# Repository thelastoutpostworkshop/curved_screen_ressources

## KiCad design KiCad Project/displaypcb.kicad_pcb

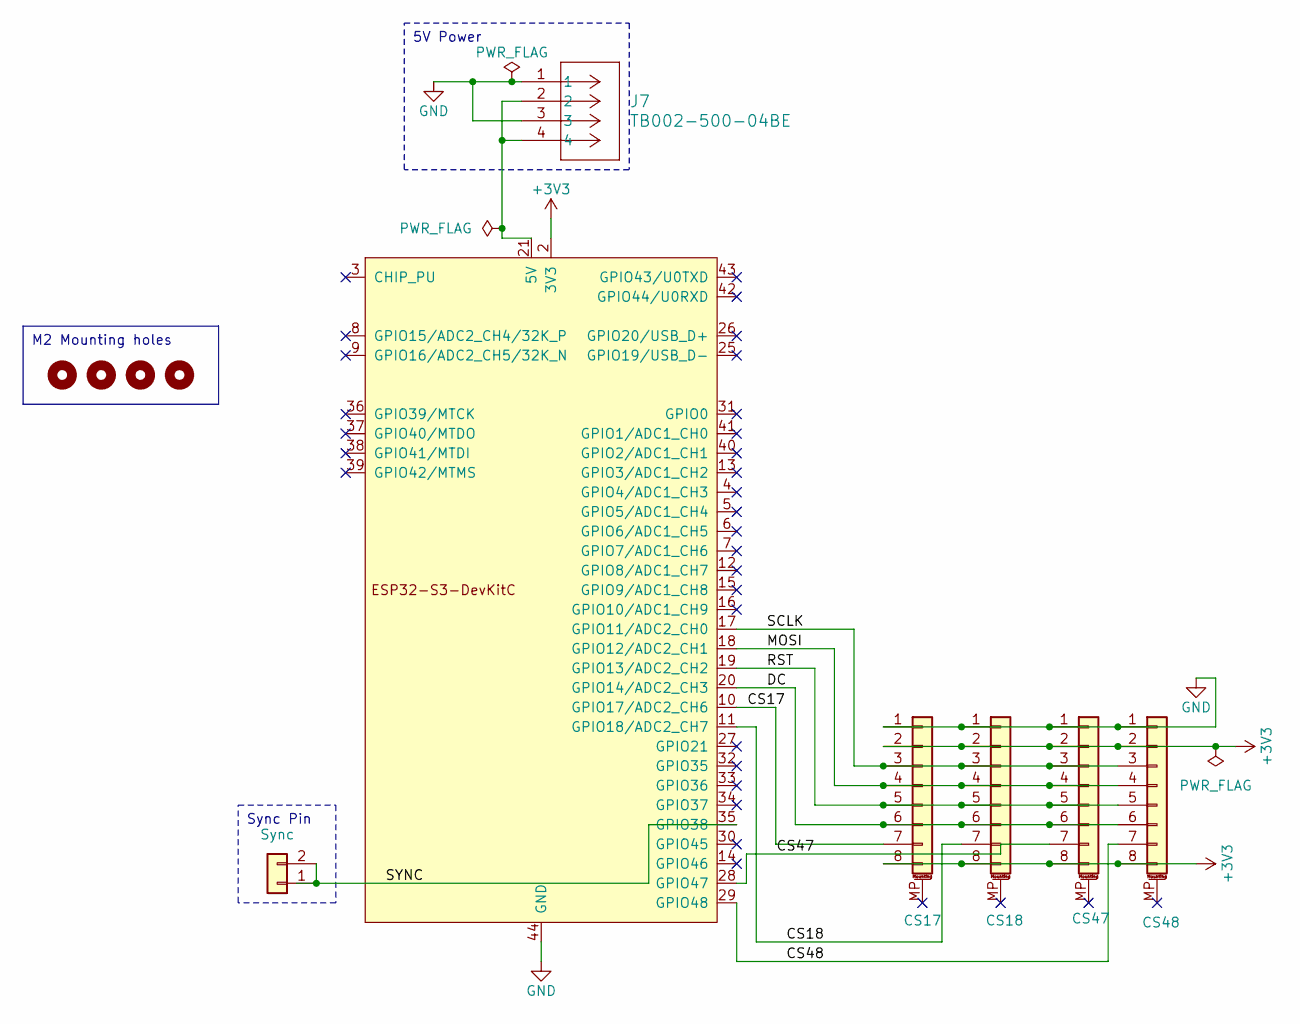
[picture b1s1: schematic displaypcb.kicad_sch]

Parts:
H1, H2, H3, H4: MountingHole; MountingHole_3.5mm
J1: CS17; PinHeader_1x08_P2.54mm_Vertical
J2: CS18; PinHeader_1x08_P2.54mm_Vertical
J3: CS47; PinHeader_1x08_P2.54mm_Vertical
J4: CS48; PinHeader_1x08_P2.54mm_Vertical
J6: Sync; PinHeader_1x02_P2.54mm_Vertical
J7: TB002-500-04BE; CONN4_TB002-500_787x299_CUD
U2: ESP32-S3-DevKitC

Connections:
+3V3: J1.2, J1.8, J2.2, J2.8, J3.2, J3.8, J4.2, J4.8, U2.1 (3V3), U2.2 (3V3)
/CS17: J1.7, U2.10 (GPIO17/ADC2_CH6)
/CS18: J2.7, U2.11 (GPIO18/ADC2_CH7)
/CS47: J3.7, U2.28 (GPIO47)
/CS48: J4.7, U2.29 (GPIO48)
/DC: J1.6, J2.6, J3.6, J4.6, U2.20 (GPIO14/ADC2_CH3)
/MOSI: J1.4, J2.4, J3.4, J4.4, U2.18 (GPIO12/ADC2_CH1)
/RST: J1.5, J2.5, J3.5, J4.5, U2.19 (GPIO13/ADC2_CH2)
/SCLK: J1.3, J2.3, J3.3, J4.3, U2.17 (GPIO11/ADC2_CH0)
/SYNC: J6.1, J6.2, U2.35 (GPIO38)
GND: J1.1, J2.1, J3.1, J4.1, J7.1, J7.3, U2.22 (GND), U2.23 (GND), U2.24 (GND), U2.44 (GND)
unnamed: J7.2, J7.4, U2.21 (5V)

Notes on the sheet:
M2 Mounting holes
Sync Pin
5V Power

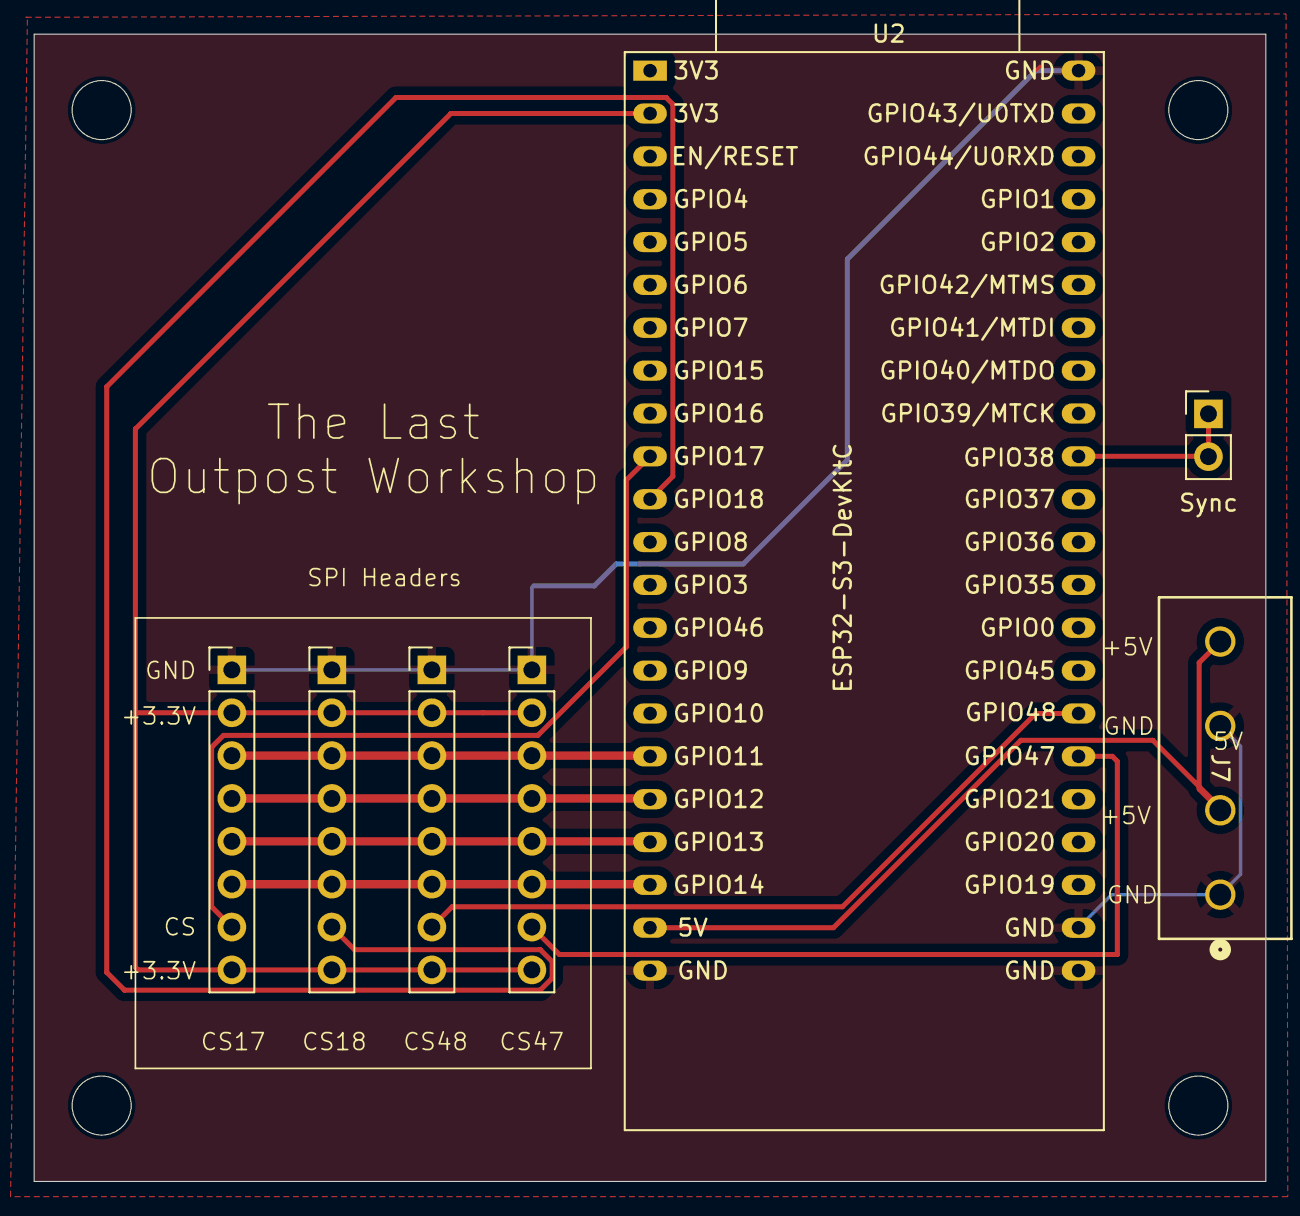
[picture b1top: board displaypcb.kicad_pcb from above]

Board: 2 copper layers, 73.0 x 68.0 mm, 11 parts (0 on the bottom side), 12 nets.
